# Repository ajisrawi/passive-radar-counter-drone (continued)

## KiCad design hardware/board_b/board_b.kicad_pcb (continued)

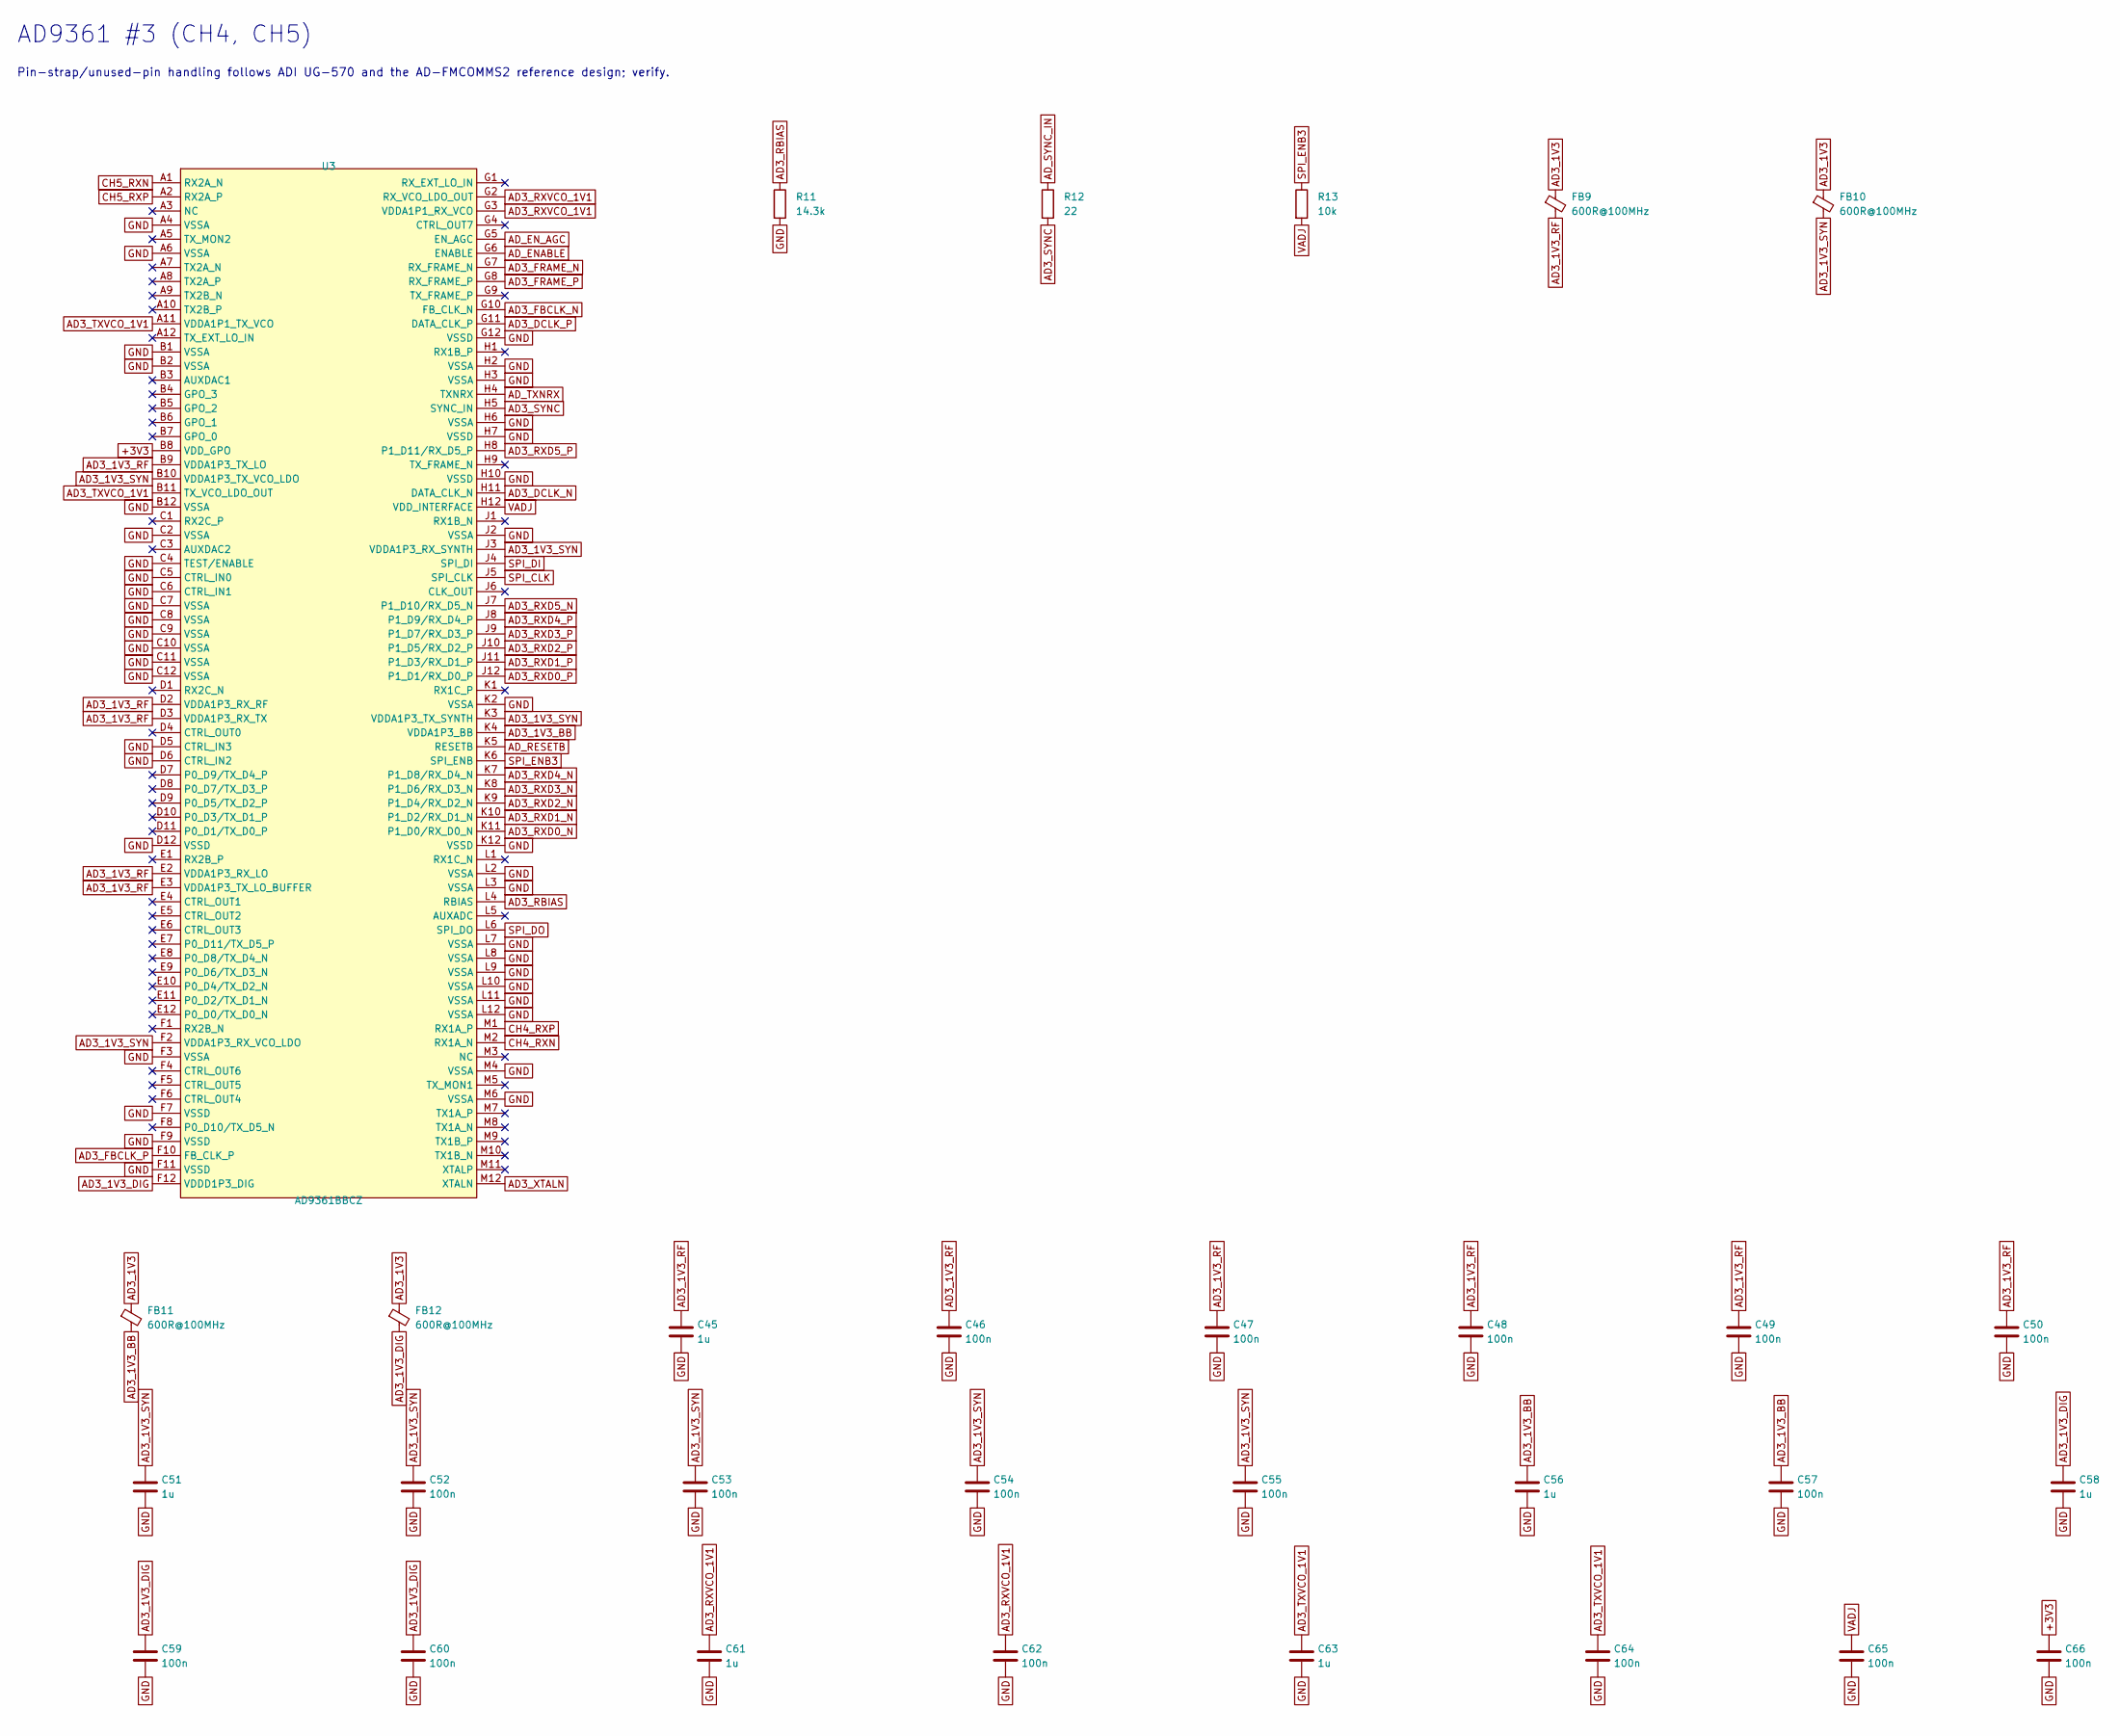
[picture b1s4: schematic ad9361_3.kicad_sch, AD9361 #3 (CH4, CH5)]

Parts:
C45, C51, C56, C58, C61, C63: 1u; C_0402_1005Metric; LCSC C52923
C46, C47, C48, C49, C50, C52, C53, C54, C55, C57, C59, C60, C62, C64, C65, C66: 100n; C_0402_1005Metric; LCSC C1525
FB9, FB10, FB11, FB12: 600R@100MHz; L_0603_1608Metric
R11: 14.3k; R_0402_1005Metric; Tolerance 1%
R12: 22; R_0402_1005Metric
R13: 10k; R_0402_1005Metric; LCSC C25744
U3: AD9361BBCZ; CSPBGA-144_L10.0-W10.0-R12-C12-P0.80-BL; MPN AD9361BBCZ; LCSC C515884

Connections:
+3V3: C66.1, U3.B8 (VDD_GPO); also elsewhere on the board
AD3_1V3: FB9.1, FB10.1, FB11.1, FB12.1; also elsewhere on the board
AD3_1V3_BB: C56.1, C57.1, FB11.2, U3.K4 (VDDA1P3_BB)
AD3_1V3_DIG: C58.1, C59.1, C60.1, FB12.2, U3.F12 (VDDD1P3_DIG)
AD3_1V3_RF: C45.1, C46.1, C47.1, C48.1, C49.1, C50.1, FB9.2, U3.B9 (VDDA1P3_TX_LO), U3.D2 (VDDA1P3_RX_RF), U3.D3 (VDDA1P3_RX_TX), U3.E2 (VDDA1P3_RX_LO), U3.E3 (VDDA1P3_TX_LO_BUFFER)
AD3_1V3_SYN: C51.1, C52.1, C53.1, C54.1, C55.1, FB10.2, U3.B10 (VDDA1P3_TX_VCO_LDO), U3.F2 (VDDA1P3_RX_VCO_LDO), U3.J3 (VDDA1P3_RX_SYNTH), U3.K3 (VDDA1P3_TX_SYNTH)
AD3_DCLK_N: U3.H11 (DATA_CLK_N); also elsewhere on the board
AD3_DCLK_P: U3.G11 (DATA_CLK_P); also elsewhere on the board
AD3_FBCLK_N: U3.G10 (FB_CLK_N); also elsewhere on the board
AD3_FBCLK_P: U3.F10 (FB_CLK_P); also elsewhere on the board
AD3_FRAME_N: U3.G7 (RX_FRAME_N); also elsewhere on the board
AD3_FRAME_P: U3.G8 (RX_FRAME_P); also elsewhere on the board
AD3_RBIAS: R11.1, U3.L4 (RBIAS)
AD3_RXD0_N: U3.K11 (P1_D0/RX_D0_N); also elsewhere on the board
AD3_RXD0_P: U3.J12 (P1_D1/RX_D0_P); also elsewhere on the board
AD3_RXD1_N: U3.K10 (P1_D2/RX_D1_N); also elsewhere on the board
AD3_RXD1_P: U3.J11 (P1_D3/RX_D1_P); also elsewhere on the board
AD3_RXD2_N: U3.K9 (P1_D4/RX_D2_N); also elsewhere on the board
AD3_RXD2_P: U3.J10 (P1_D5/RX_D2_P); also elsewhere on the board
AD3_RXD3_N: U3.K8 (P1_D6/RX_D3_N); also elsewhere on the board
AD3_RXD3_P: U3.J9 (P1_D7/RX_D3_P); also elsewhere on the board
AD3_RXD4_N: U3.K7 (P1_D8/RX_D4_N); also elsewhere on the board
AD3_RXD4_P: U3.J8 (P1_D9/RX_D4_P); also elsewhere on the board
AD3_RXD5_N: U3.J7 (P1_D10/RX_D5_N); also elsewhere on the board
AD3_RXD5_P: U3.H8 (P1_D11/RX_D5_P); also elsewhere on the board
AD3_RXVCO_1V1: C61.1, C62.1, U3.G2 (RX_VCO_LDO_OUT), U3.G3 (VDDA1P1_RX_VCO)
AD3_SYNC: R12.2, U3.H5 (SYNC_IN)
AD3_TXVCO_1V1: C63.1, C64.1, U3.A11 (VDDA1P1_TX_VCO), U3.B11 (TX_VCO_LDO_OUT)
AD3_XTALN: U3.M12 (XTALN); also elsewhere on the board
AD_ENABLE: U3.G6 (ENABLE); also elsewhere on the board
AD_EN_AGC: U3.G5 (EN_AGC); also elsewhere on the board
AD_RESETB: U3.K5 (RESETB); also elsewhere on the board
AD_SYNC_IN: R12.1; also elsewhere on the board
AD_TXNRX: U3.H4 (TXNRX); also elsewhere on the board
CH4_RXN: U3.M2 (RX1A_N); also elsewhere on the board
CH4_RXP: U3.M1 (RX1A_P); also elsewhere on the board
CH5_RXN: U3.A1 (RX2A_N); also elsewhere on the board
CH5_RXP: U3.A2 (RX2A_P); also elsewhere on the board
GND: C45.2, C46.2, C47.2, C48.2, C49.2, C50.2, C51.2, C52.2, C53.2, C54.2, C55.2, C56.2, C57.2, C58.2, C59.2, C60.2, C61.2, C62.2, C63.2, C64.2, C65.2, C66.2, R11.2, U3.A4 (VSSA), U3.A6 (VSSA), U3.B1 (VSSA), U3.B2 (VSSA), U3.B12 (VSSA), U3.C2 (VSSA), U3.C4 (TEST/ENABLE), U3.C5 (CTRL_IN0), U3.C6 (CTRL_IN1), U3.C7 (VSSA), U3.C8 (VSSA), U3.C9 (VSSA), U3.C10 (VSSA), U3.C11 (VSSA), U3.C12 (VSSA), U3.D5 (CTRL_IN3), U3.D6 (CTRL_IN2), U3.D12 (VSSD), U3.F3 (VSSA), U3.F7 (VSSD), U3.F9 (VSSD), U3.F11 (VSSD), U3.G12 (VSSD), U3.H2 (VSSA), U3.H3 (VSSA), U3.H6 (VSSA), U3.H7 (VSSD), U3.H10 (VSSD), U3.J2 (VSSA), U3.K2 (VSSA), U3.K12 (VSSD), U3.L2 (VSSA), U3.L3 (VSSA), U3.L7 (VSSA), U3.L8 (VSSA), U3.L9 (VSSA), U3.L10 (VSSA), U3.L11 (VSSA), U3.L12 (VSSA), U3.M4 (VSSA), U3.M6 (VSSA); also elsewhere on the board
SPI_CLK: U3.J5 (SPI_CLK); also elsewhere on the board
SPI_DI: U3.J4 (SPI_DI); also elsewhere on the board
SPI_DO: U3.L6 (SPI_DO); also elsewhere on the board
SPI_ENB3: R13.1, U3.K6 (SPI_ENB); also elsewhere on the board
VADJ: C65.1, R13.2, U3.H12 (VDD_INTERFACE); also elsewhere on the board

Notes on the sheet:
AD9361 #3 (CH4, CH5)
Pin-strap/unused-pin handling follows ADI UG-570 and the AD-FMCOMMS2 reference design; verify.

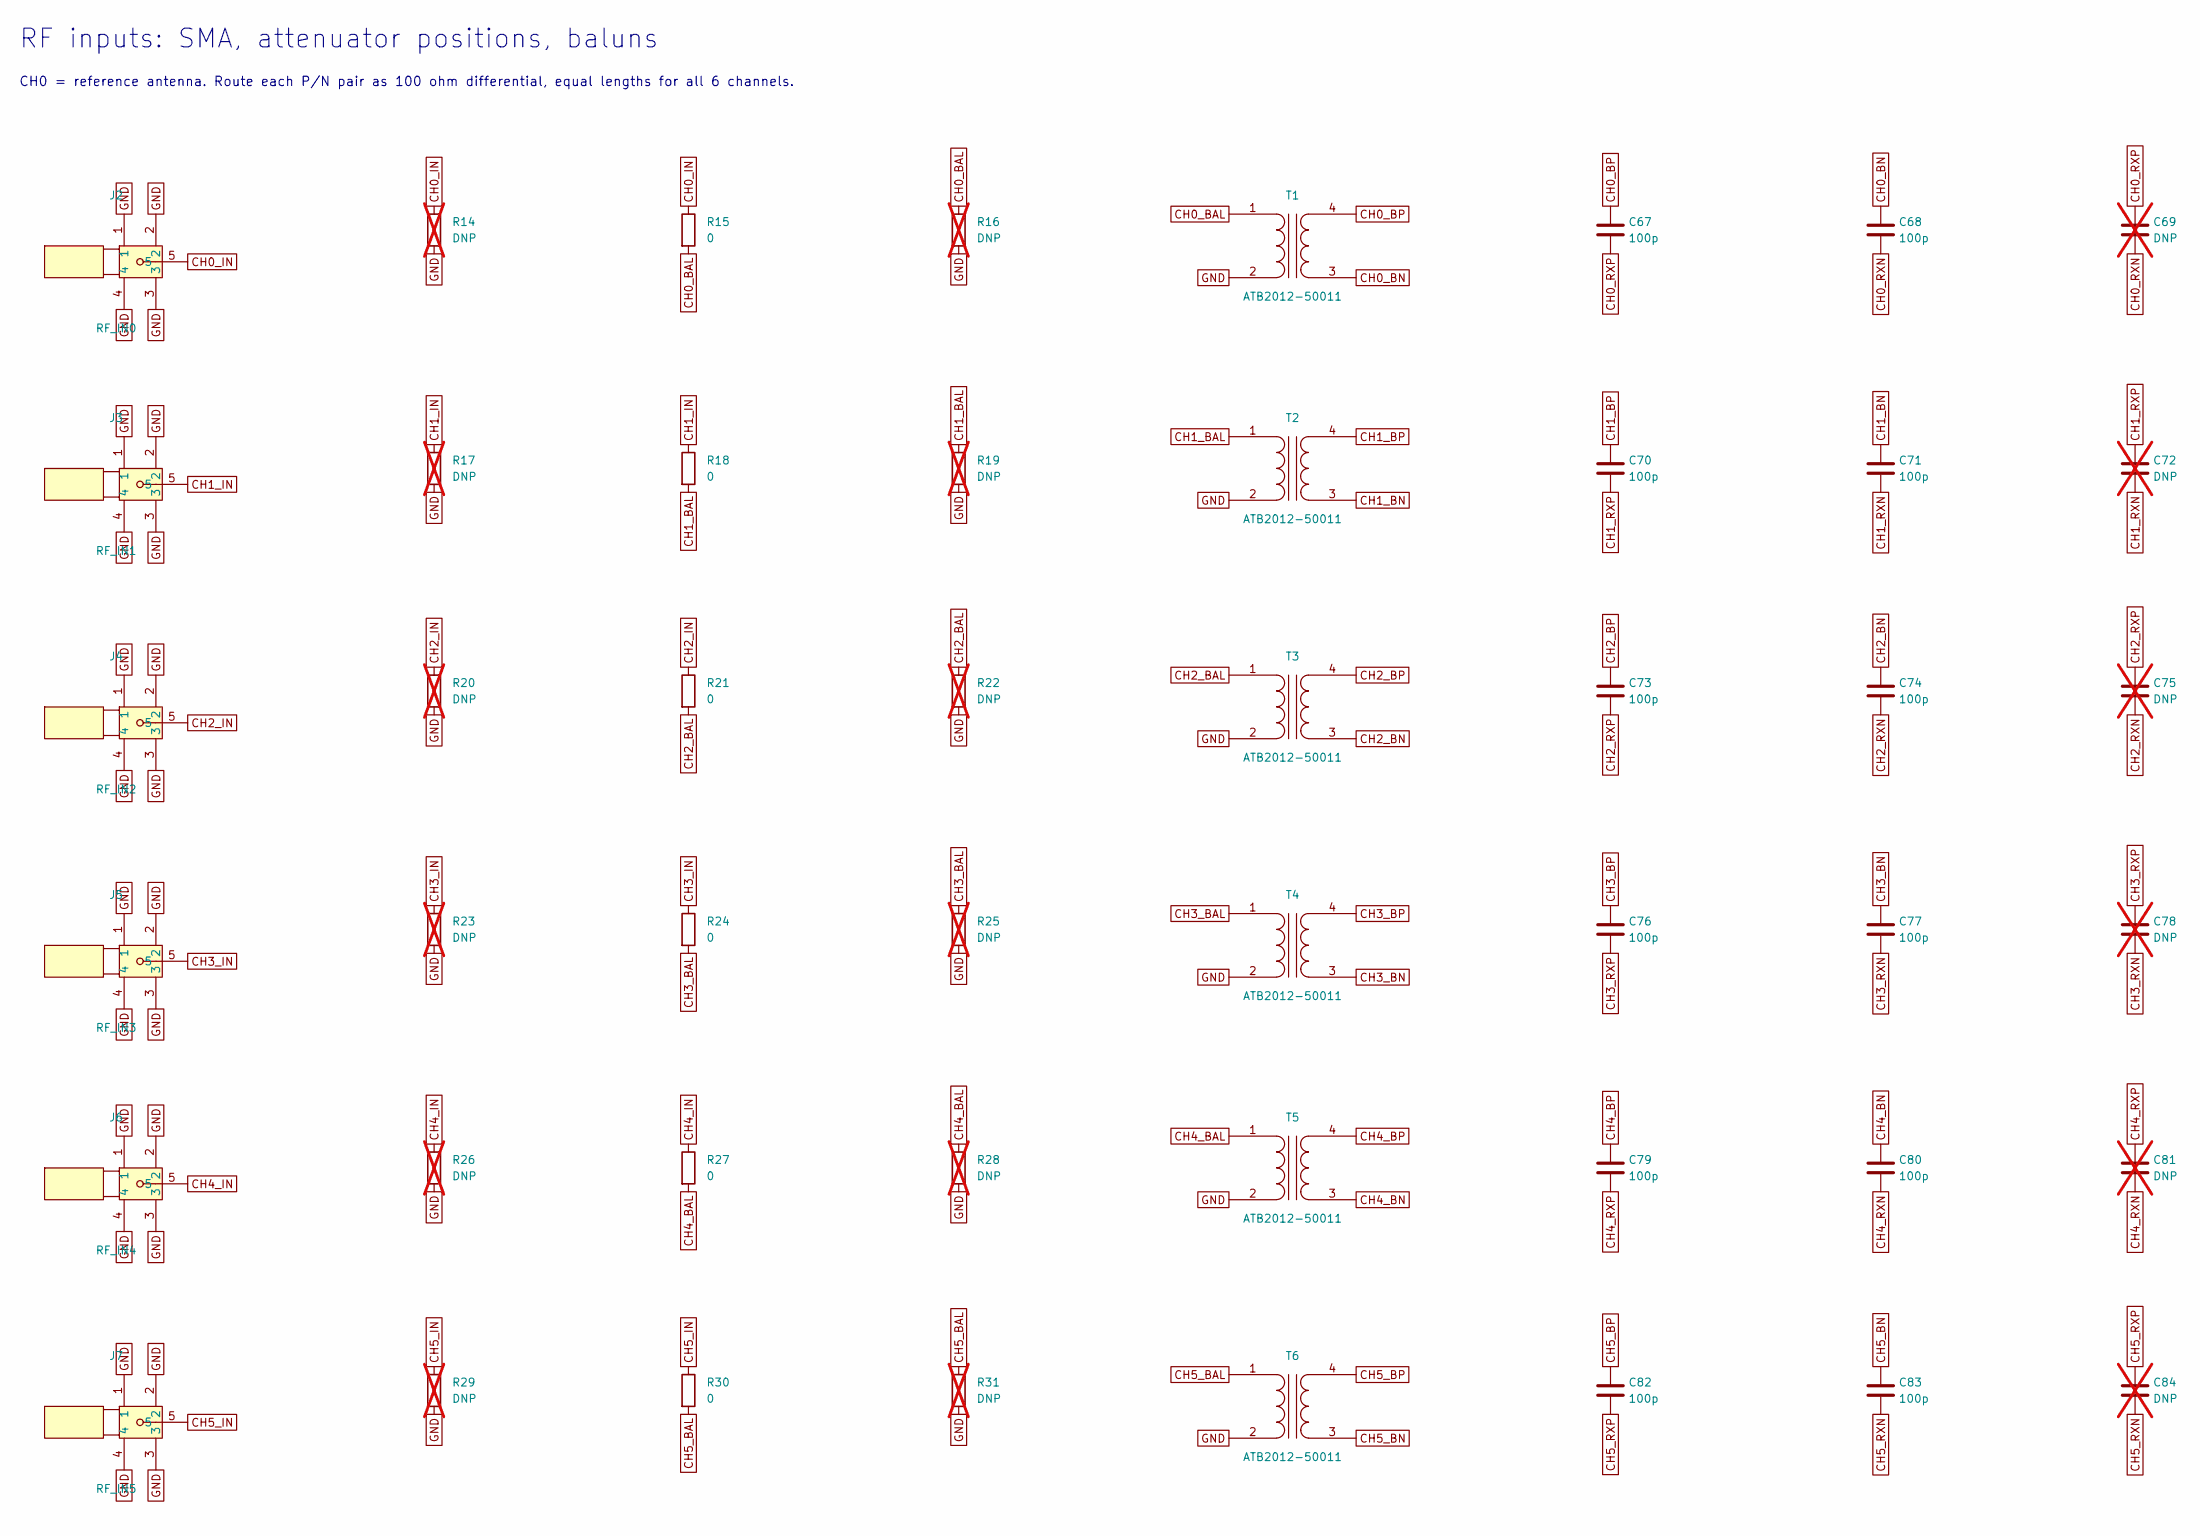
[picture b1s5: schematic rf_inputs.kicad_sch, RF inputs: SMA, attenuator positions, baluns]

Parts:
C67, C68, C70, C71, C73, C74, C76, C77, C79, C80, C82, C83: 100p; C_0402_1005Metric
C69, C72, C75, C78, C81, C84: DNP; C_0402_1005Metric; not fitted
J2: RF_IN0; SMA-TH_BWSMA-KE-Z001; MPN BWSMA-KE-Z001; LCSC C496549
J3: RF_IN1; SMA-TH_BWSMA-KE-Z001; MPN BWSMA-KE-Z001; LCSC C496549
J4: RF_IN2; SMA-TH_BWSMA-KE-Z001; MPN BWSMA-KE-Z001; LCSC C496549
J5: RF_IN3; SMA-TH_BWSMA-KE-Z001; MPN BWSMA-KE-Z001; LCSC C496549
J6: RF_IN4; SMA-TH_BWSMA-KE-Z001; MPN BWSMA-KE-Z001; LCSC C496549
J7: RF_IN5; SMA-TH_BWSMA-KE-Z001; MPN BWSMA-KE-Z001; LCSC C496549
R14, R16, R17, R19, R20, R22, R23, R25, R26, R28, R29, R31: DNP; R_0402_1005Metric; not fitted
R15, R18, R21, R24, R27, R30: 0; R_0402_1005Metric; LCSC C17168
T1, T2, T3, T4, T5, T6: ATB2012-50011; XFMR-SMD_ATB2012-50011-T000; MPN ATB2012-50011-T000; LCSC C92015

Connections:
CH0_BAL: R15.2, R16.1, T1.1 (AA)
CH0_BN: C68.1, T1.3 (SA)
CH0_BP: C67.1, T1.4 (SB)
CH0_IN: J2.5, R14.1, R15.1
CH0_RXN: C68.2, C69.2; also elsewhere on the board
CH0_RXP: C67.2, C69.1; also elsewhere on the board
CH1_BAL: R18.2, R19.1, T2.1 (AA)
CH1_BN: C71.1, T2.3 (SA)
CH1_BP: C70.1, T2.4 (SB)
CH1_IN: J3.5, R17.1, R18.1
CH1_RXN: C71.2, C72.2; also elsewhere on the board
CH1_RXP: C70.2, C72.1; also elsewhere on the board
CH2_BAL: R21.2, R22.1, T3.1 (AA)
CH2_BN: C74.1, T3.3 (SA)
CH2_BP: C73.1, T3.4 (SB)
CH2_IN: J4.5, R20.1, R21.1
CH2_RXN: C74.2, C75.2; also elsewhere on the board
CH2_RXP: C73.2, C75.1; also elsewhere on the board
CH3_BAL: R24.2, R25.1, T4.1 (AA)
CH3_BN: C77.1, T4.3 (SA)
CH3_BP: C76.1, T4.4 (SB)
CH3_IN: J5.5, R23.1, R24.1
CH3_RXN: C77.2, C78.2; also elsewhere on the board
CH3_RXP: C76.2, C78.1; also elsewhere on the board
CH4_BAL: R27.2, R28.1, T5.1 (AA)
CH4_BN: C80.1, T5.3 (SA)
CH4_BP: C79.1, T5.4 (SB)
CH4_IN: J6.5, R26.1, R27.1
CH4_RXN: C80.2, C81.2; also elsewhere on the board
CH4_RXP: C79.2, C81.1; also elsewhere on the board
CH5_BAL: R30.2, R31.1, T6.1 (AA)
CH5_BN: C83.1, T6.3 (SA)
CH5_BP: C82.1, T6.4 (SB)
CH5_IN: J7.5, R29.1, R30.1
CH5_RXN: C83.2, C84.2; also elsewhere on the board
CH5_RXP: C82.2, C84.1; also elsewhere on the board
GND: J2.1, J2.2, J2.3, J2.4, J3.1, J3.2, J3.3, J3.4, J4.1, J4.2, J4.3, J4.4, J5.1, J5.2, J5.3, J5.4, J6.1, J6.2, J6.3, J6.4, J7.1, J7.2, J7.3, J7.4, R14.2, R16.2, R17.2, R19.2, R20.2, R22.2, R23.2, R25.2, R26.2, R28.2, R29.2, R31.2, T1.2 (AB), T2.2 (AB), T3.2 (AB), T4.2 (AB), T5.2 (AB), T6.2 (AB); also elsewhere on the board

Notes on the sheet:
RF inputs: SMA, attenuator positions, baluns
CH0 = reference antenna. Route each P/N pair as 100 ohm differential, equal lengths for all 6 channels.

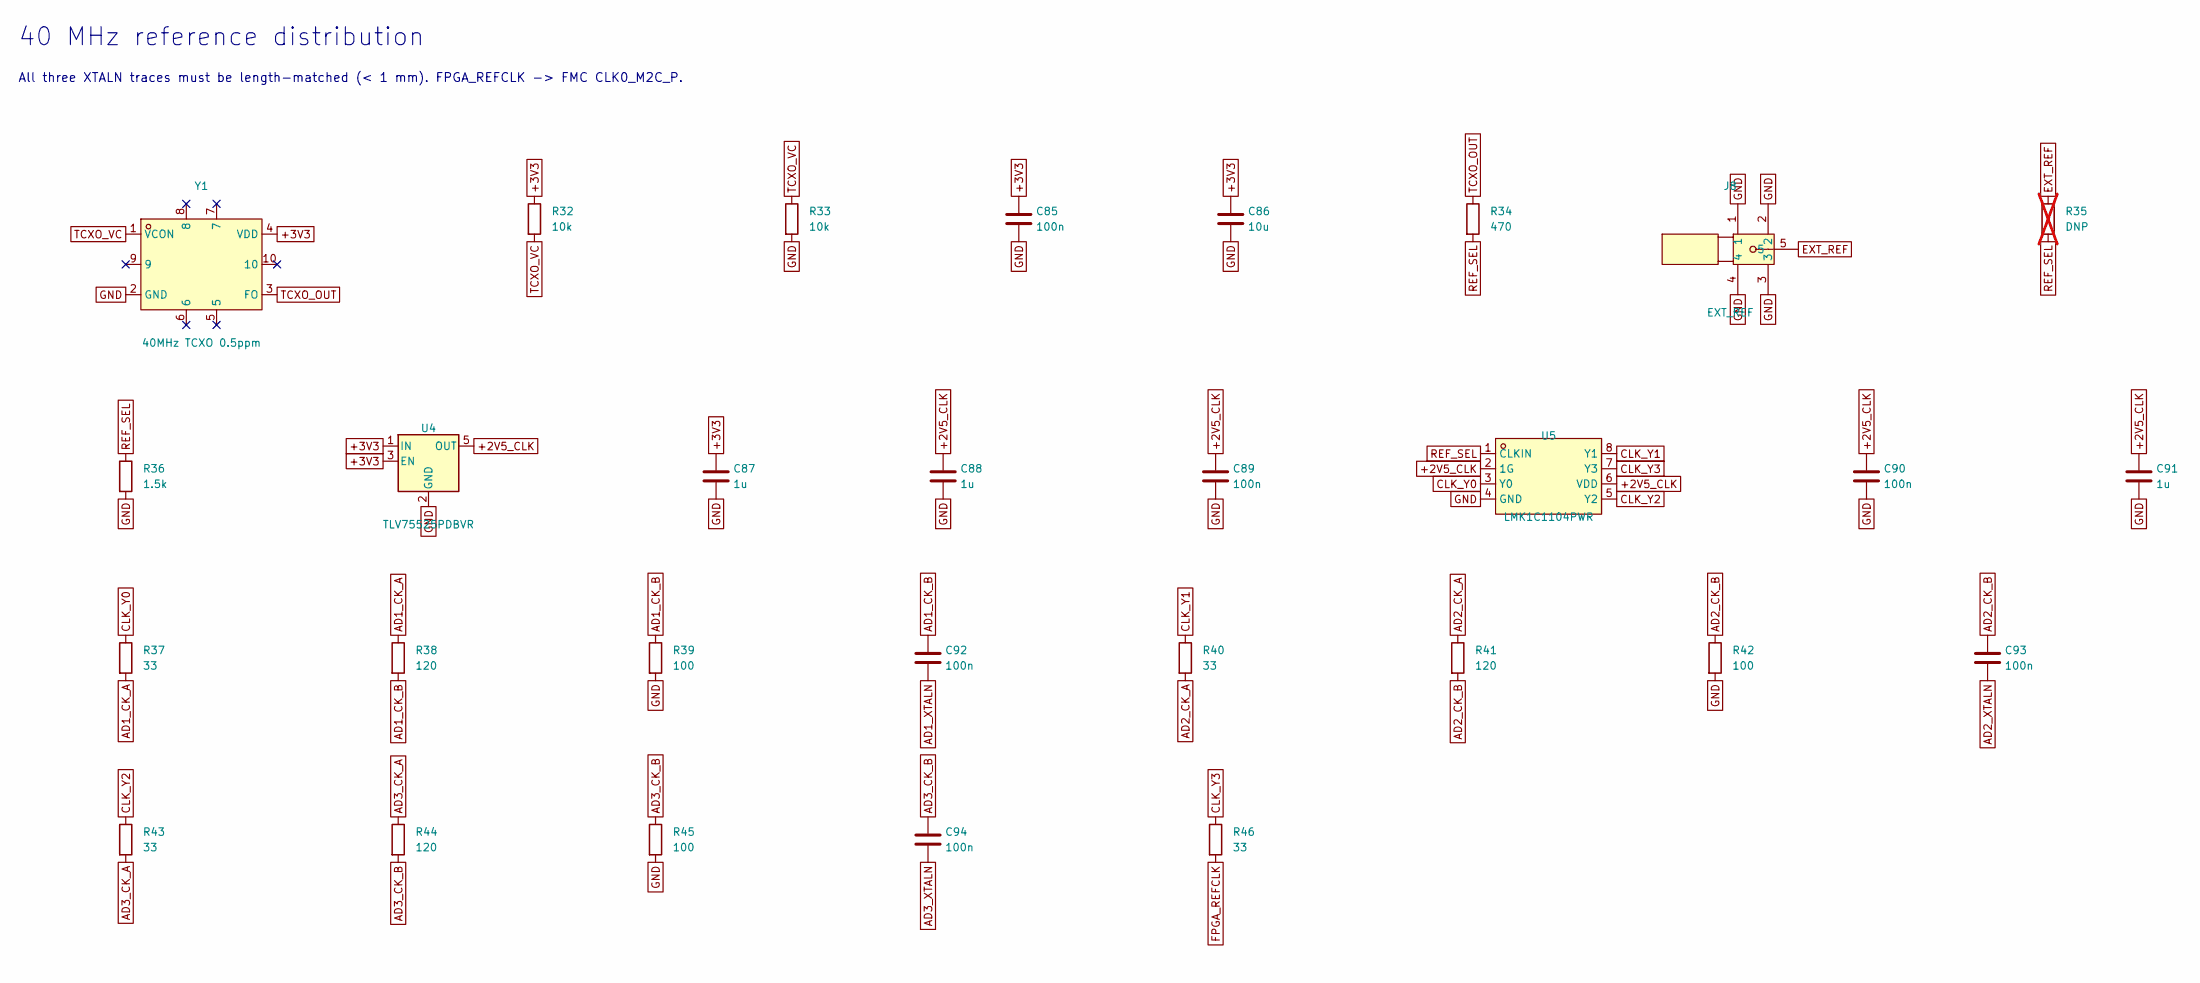
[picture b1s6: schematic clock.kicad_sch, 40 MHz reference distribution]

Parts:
C85, C89, C90, C92, C93, C94: 100n; C_0402_1005Metric; LCSC C1525
C86: 10u; C_0603_1608Metric; LCSC C19702
C87, C88, C91: 1u; C_0402_1005Metric; LCSC C52923
J8: EXT_REF; SMA-TH_BWSMA-KE-Z001; MPN BWSMA-KE-Z001; LCSC C496549
R32, R33: 10k; R_0402_1005Metric; LCSC C25744
R34: 470; R_0402_1005Metric
R35: DNP; R_0402_1005Metric; not fitted
R36: 1.5k; R_0402_1005Metric
R37, R40, R43, R46: 33; R_0402_1005Metric
R38, R41, R44: 120; R_0402_1005Metric
R39, R42, R45: 100; R_0402_1005Metric
U4: TLV75525PDBVR; SOT-23-5
U5: LMK1C1104PWR; TSSOP-8_L4.4-W3.0-P0.65-LS6.4-TL; MPN LMK1C1104PWR; LCSC C1855734
Y1: 40MHz TCXO 0.5ppm; OSC-SMD_10P-L7.0-W5.0-BL; MPN BT0507BH3I507BN40B; LCSC C516506

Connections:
+2V5_CLK: C88.1, C89.1, C90.1, C91.1, U4.5 (OUT), U5.2 (1G), U5.6 (VDD)
+3V3: C85.1, C86.1, C87.1, R32.1, U4.1 (IN), U4.3 (EN), Y1.4 (VDD); also elsewhere on the board
AD1_CK_A: R37.2, R38.1
AD1_CK_B: C92.1, R38.2, R39.1
AD1_XTALN: C92.2; also elsewhere on the board
AD2_CK_A: R40.2, R41.1
AD2_CK_B: C93.1, R41.2, R42.1
AD2_XTALN: C93.2; also elsewhere on the board
AD3_CK_A: R43.2, R44.1
AD3_CK_B: C94.1, R44.2, R45.1
AD3_XTALN: C94.2; also elsewhere on the board
CLK_Y0: R37.1, U5.3 (Y0)
CLK_Y1: R40.1, U5.8 (Y1)
CLK_Y2: R43.1, U5.5 (Y2)
CLK_Y3: R46.1, U5.7 (Y3)
EXT_REF: J8.5, R35.1
FPGA_REFCLK: R46.2; also elsewhere on the board
GND: C85.2, C86.2, C87.2, C88.2, C89.2, C90.2, C91.2, J8.1, J8.2, J8.3, J8.4, R33.2, R36.2, R39.2, R42.2, R45.2, U4.2 (GND), U5.4 (GND), Y1.2 (GND); also elsewhere on the board
REF_SEL: R34.2, R35.2, R36.1, U5.1 (CLKIN)
TCXO_OUT: R34.1, Y1.3 (FO)
TCXO_VC: R32.2, R33.1, Y1.1 (VCON)

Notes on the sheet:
40 MHz reference distribution
All three XTALN traces must be length-matched (< 1 mm). FPGA_REFCLK -> FMC CLK0_M2C_P.

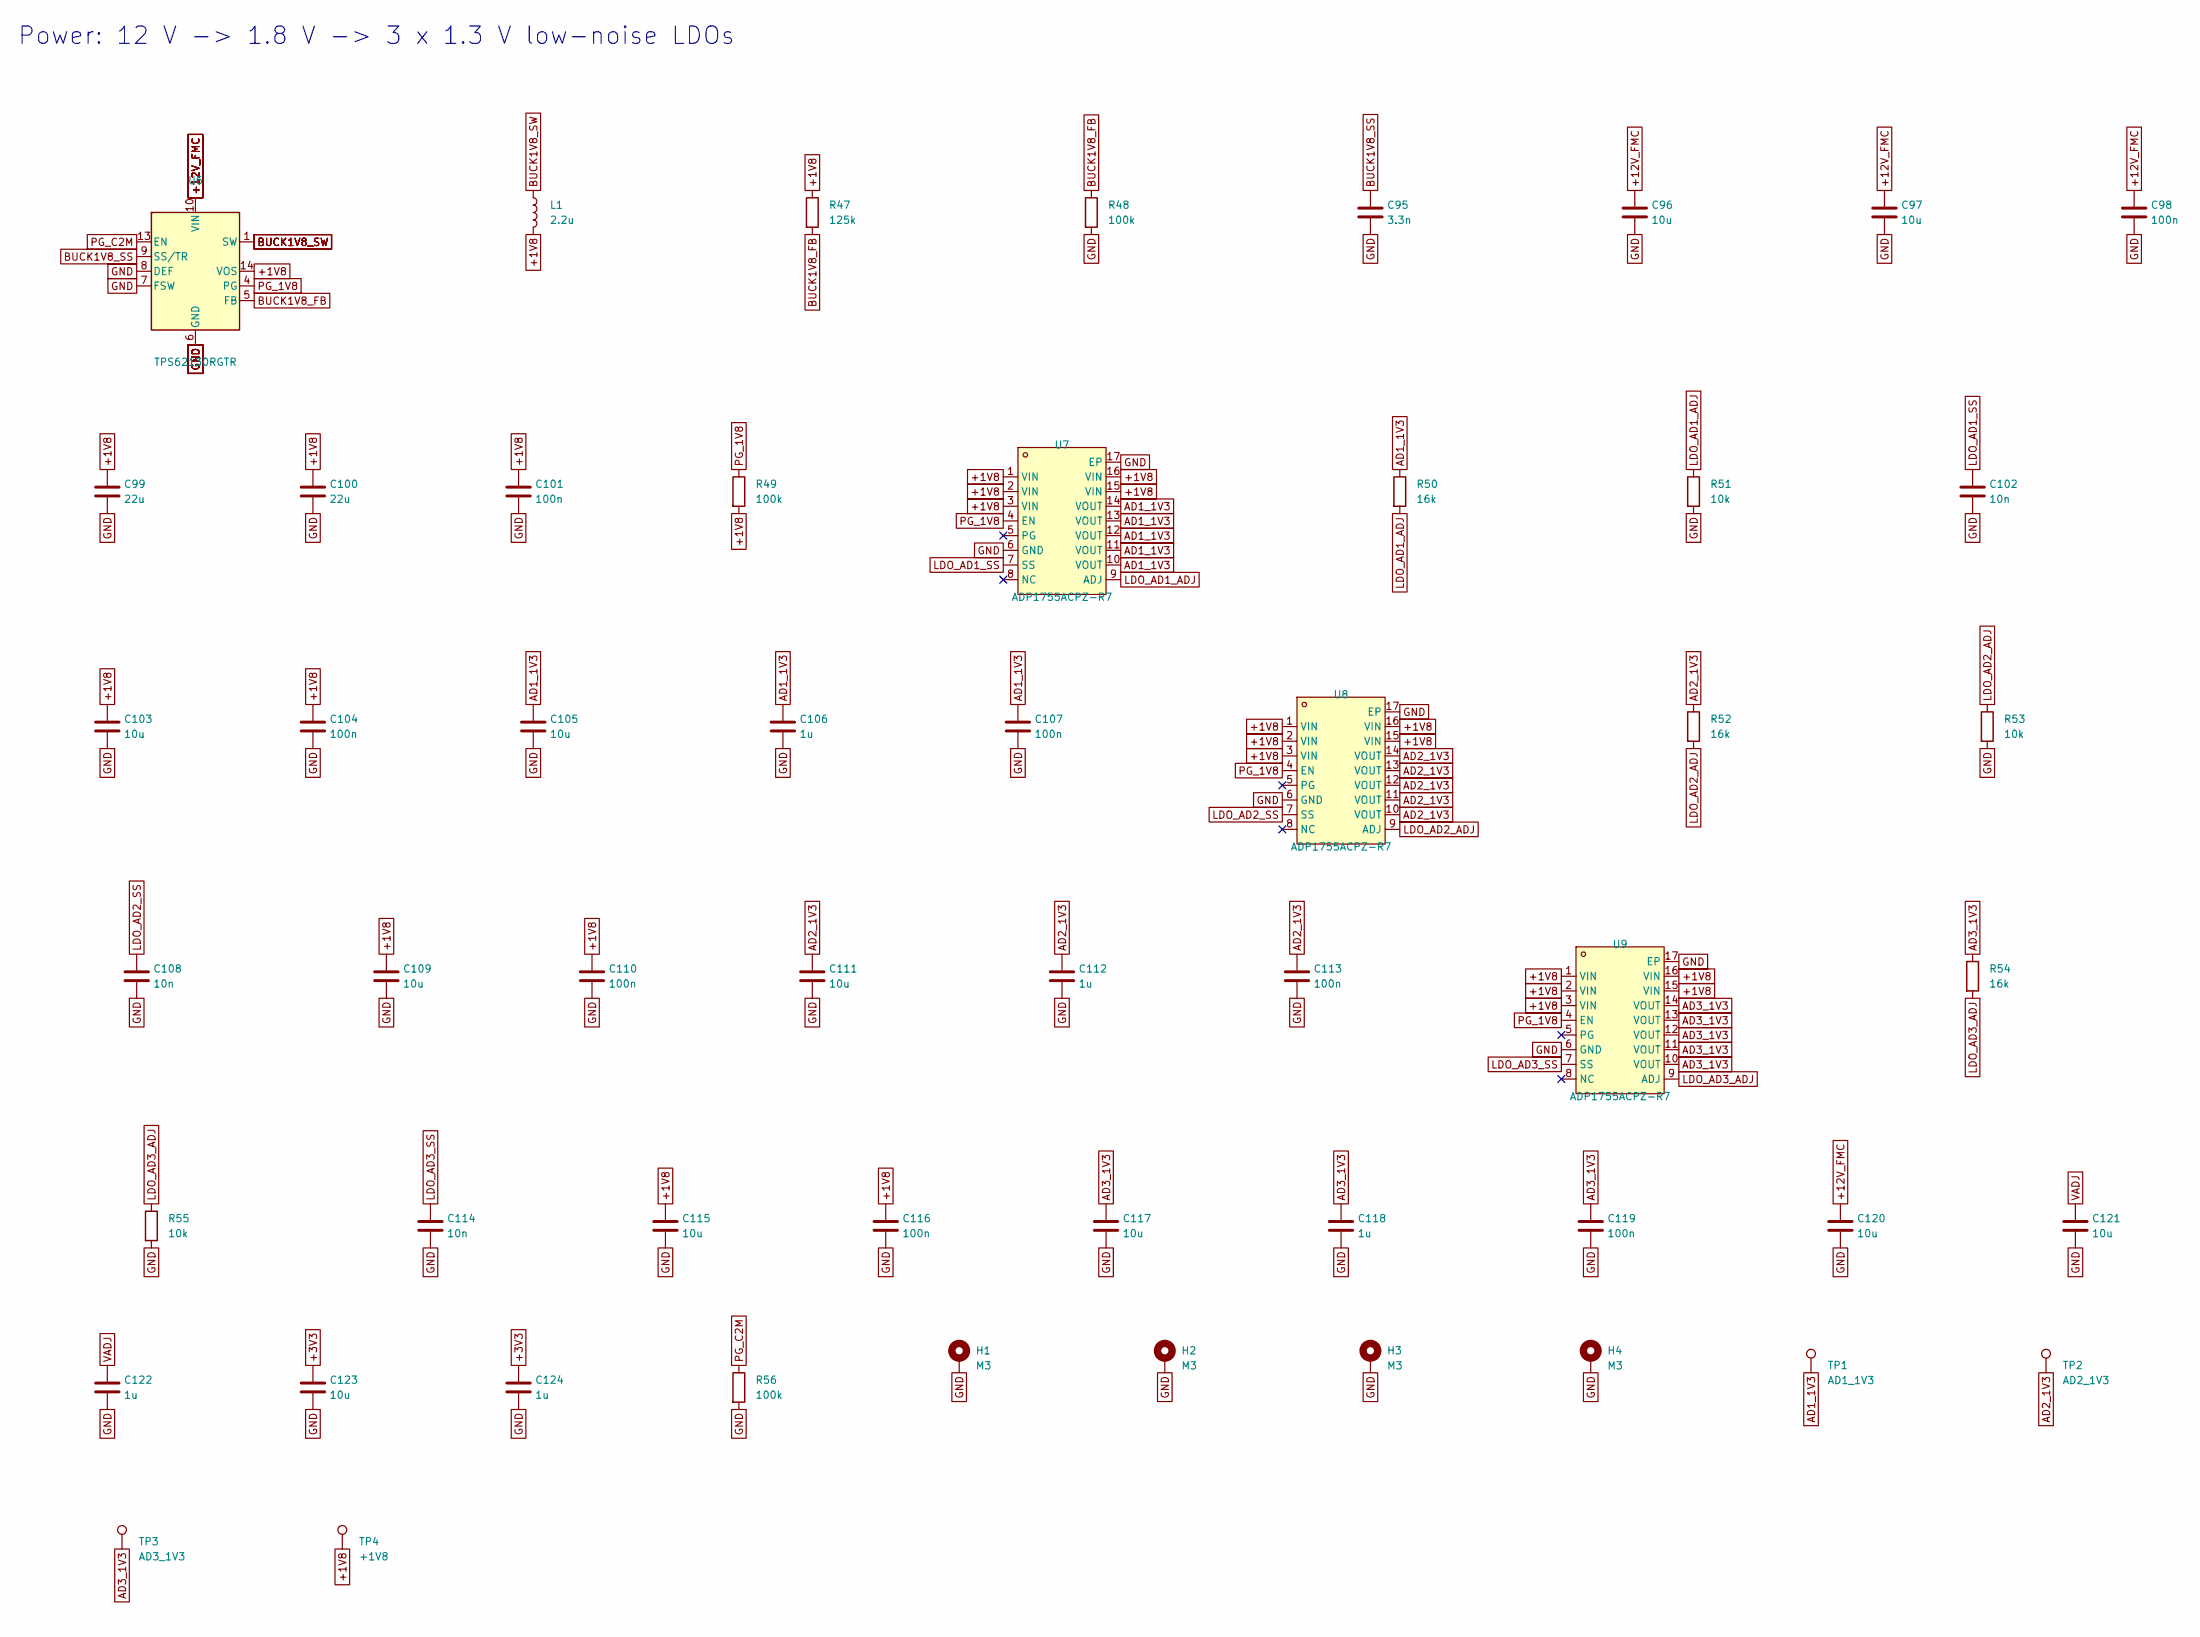
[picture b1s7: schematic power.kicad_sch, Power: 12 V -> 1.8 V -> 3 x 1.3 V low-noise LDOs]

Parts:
C95: 3.3n; C_0402_1005Metric
C96, C97, C120: 10u; C_0805_2012Metric
C98, C101, C104, C107, C110, C113, C116, C119: 100n; C_0402_1005Metric; LCSC C1525
C99, C100: 22u; C_0805_2012Metric; LCSC C45783
C102, C108, C114: 10n; C_0402_1005Metric; LCSC C15195
C103, C105, C109, C111, C115, C117, C121, C123: 10u; C_0603_1608Metric; LCSC C19702
C106, C112, C118, C122, C124: 1u; C_0402_1005Metric; LCSC C52923
H1, H2, H3, H4: M3; MountingHole_3.2mm_M3_Pad_Via
L1: 2.2u; L_Bourns-SRN4018; MPN SRN4018-2R2M
R47: 125k; R_0402_1005Metric
R48, R49, R56: 100k; R_0402_1005Metric; LCSC C25741
R50, R52, R54: 16k; R_0402_1005Metric; Tolerance 1%
R51, R53, R55: 10k; R_0402_1005Metric; Tolerance 1%; LCSC C25744
TP1: AD1_1V3; TestPoint_Pad_D1.0mm
TP2: AD2_1V3; TestPoint_Pad_D1.0mm
TP3: AD3_1V3; TestPoint_Pad_D1.0mm
TP4: +1V8; TestPoint_Pad_D1.0mm
U6: TPS62130RGTR; VQFN-16-1EP_3x3mm_P0.5mm_EP1.68x1.68mm; MPN TPS62130RGTR; LCSC C43590
U7, U8, U9: ADP1755ACPZ-R7; LFCSP-16_L4.0-W4.0-P0.65-BL-EP2.2; MPN ADP1755ACPZ-R7; LCSC C403695

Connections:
+1V8: C99.1, C100.1, C101.1, C103.1, C104.1, C109.1, C110.1, C115.1, C116.1, L1.2, R47.1, R49.2, TP4.1, U6.14 (VOS), U7.1 (VIN), U7.2 (VIN), U7.3 (VIN), U7.15 (VIN), U7.16 (VIN), U8.1 (VIN), U8.2 (VIN), U8.3 (VIN), U8.15 (VIN), U8.16 (VIN), U9.1 (VIN), U9.2 (VIN), U9.3 (VIN), U9.15 (VIN), U9.16 (VIN)
+3V3: C123.1, C124.1; also elsewhere on the board
+12V_FMC: C96.1, C97.1, C98.1, C120.1, U6.10 (VIN), U6.11 (VIN), U6.12 (VIN); also elsewhere on the board
AD1_1V3: C105.1, C106.1, C107.1, R50.1, TP1.1, U7.10 (VOUT), U7.11 (VOUT), U7.12 (VOUT), U7.13 (VOUT), U7.14 (VOUT); also elsewhere on the board
AD2_1V3: C111.1, C112.1, C113.1, R52.1, TP2.1, U8.10 (VOUT), U8.11 (VOUT), U8.12 (VOUT), U8.13 (VOUT), U8.14 (VOUT); also elsewhere on the board
AD3_1V3: C117.1, C118.1, C119.1, R54.1, TP3.1, U9.10 (VOUT), U9.11 (VOUT), U9.12 (VOUT), U9.13 (VOUT), U9.14 (VOUT); also elsewhere on the board
BUCK1V8_FB: R47.2, R48.1, U6.5 (FB)
BUCK1V8_SS: C95.1, U6.9 (SS/TR)
BUCK1V8_SW: L1.1, U6.1 (SW), U6.2 (SW), U6.3 (SW)
GND: C95.2, C96.2, C97.2, C98.2, C99.2, C100.2, C101.2, C102.2, C103.2, C104.2, C105.2, C106.2, C107.2, C108.2, C109.2, C110.2, C111.2, C112.2, C113.2, C114.2, C115.2, C116.2, C117.2, C118.2, C119.2, C120.2, C121.2, C122.2, C123.2, C124.2, H1.1, H2.1, H3.1, H4.1, R48.2, R51.2, R53.2, R55.2, R56.2, U6.6 (GND), U6.7 (FSW), U6.8 (DEF), U6.15 (GND), U6.16 (GND), U6.17 (GND), U7.6 (GND), U7.17 (EP), U8.6 (GND), U8.17 (EP), U9.6 (GND), U9.17 (EP); also elsewhere on the board
LDO_AD1_ADJ: R50.2, R51.1, U7.9 (ADJ)
LDO_AD1_SS: C102.1, U7.7 (SS)
LDO_AD2_ADJ: R52.2, R53.1, U8.9 (ADJ)
LDO_AD2_SS: C108.1, U8.7 (SS)
LDO_AD3_ADJ: R54.2, R55.1, U9.9 (ADJ)
LDO_AD3_SS: C114.1, U9.7 (SS)
PG_1V8: R49.1, U6.4 (PG), U7.4 (EN), U8.4 (EN), U9.4 (EN)
PG_C2M: R56.1, U6.13 (EN); also elsewhere on the board
VADJ: C121.1, C122.1; also elsewhere on the board

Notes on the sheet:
Power: 12 V -> 1.8 V -> 3 x 1.3 V low-noise LDOs
